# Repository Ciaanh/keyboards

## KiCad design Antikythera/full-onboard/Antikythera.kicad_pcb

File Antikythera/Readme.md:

http://www.keyboard-layout-editor.com/#/gists/16c88de775d4e0aa35cefe443daa3789

http://www.keyboard-layout-editor.com/
http://builder.swillkb.com/
https://github.com/badgeek/svg2shenzhen
inkscape
import svg in Kicad to place switches

Pin out
Atmega32u4

oled 2 pins
led 1 pin

Pro Micro

.   |  |  |  |  |  |    .
----|--|--|--|--|--|-----  
D3  |  |  |  |  |  |  RAW
D2  |  |  |  |  |  |  GND
GND |  |  |  |  |  |  RST
GND |  |  |  |  |  |  VCC
D1  |  |  |  |  |  |  F4
D0  |  |  |  |  |  |  F5
D4  |  |  |  |  |  |  F6
C6  |  |  |  |  |  |  F7
D7  |  |  |  |  |  |  B1
E6  |  |  |  |  |  |  B3
B4  |  |  |  |  |  |  B2
B5  |  |  |  |  |  |  B6

I/O => 18
15

Elite-C

.   |    |    |    |    |    |    .
----|----|----|----|----|----|-----  
D3  |    |    |    |    |    |  B0
D2  |    |    |    |    |    |  GND
GND |    |    |    |    |    |  RST
GND |    |    |    |    |    |  VCC
D1  |    |    |    |    |    |  F4
D0  |    |    |    |    |    |  F5
D4  |    |    |    |    |    |  F6
C6  |    |    |    |    |    |  F7
D7  |    |    |    |    |    |  B1
E6  |    |    |    |    |    |  B3
B4  |    |    |    |    |    |  B2
B5  | B7 | D5 | C7 | F1 | F0 |  B6

I/O => 24
21

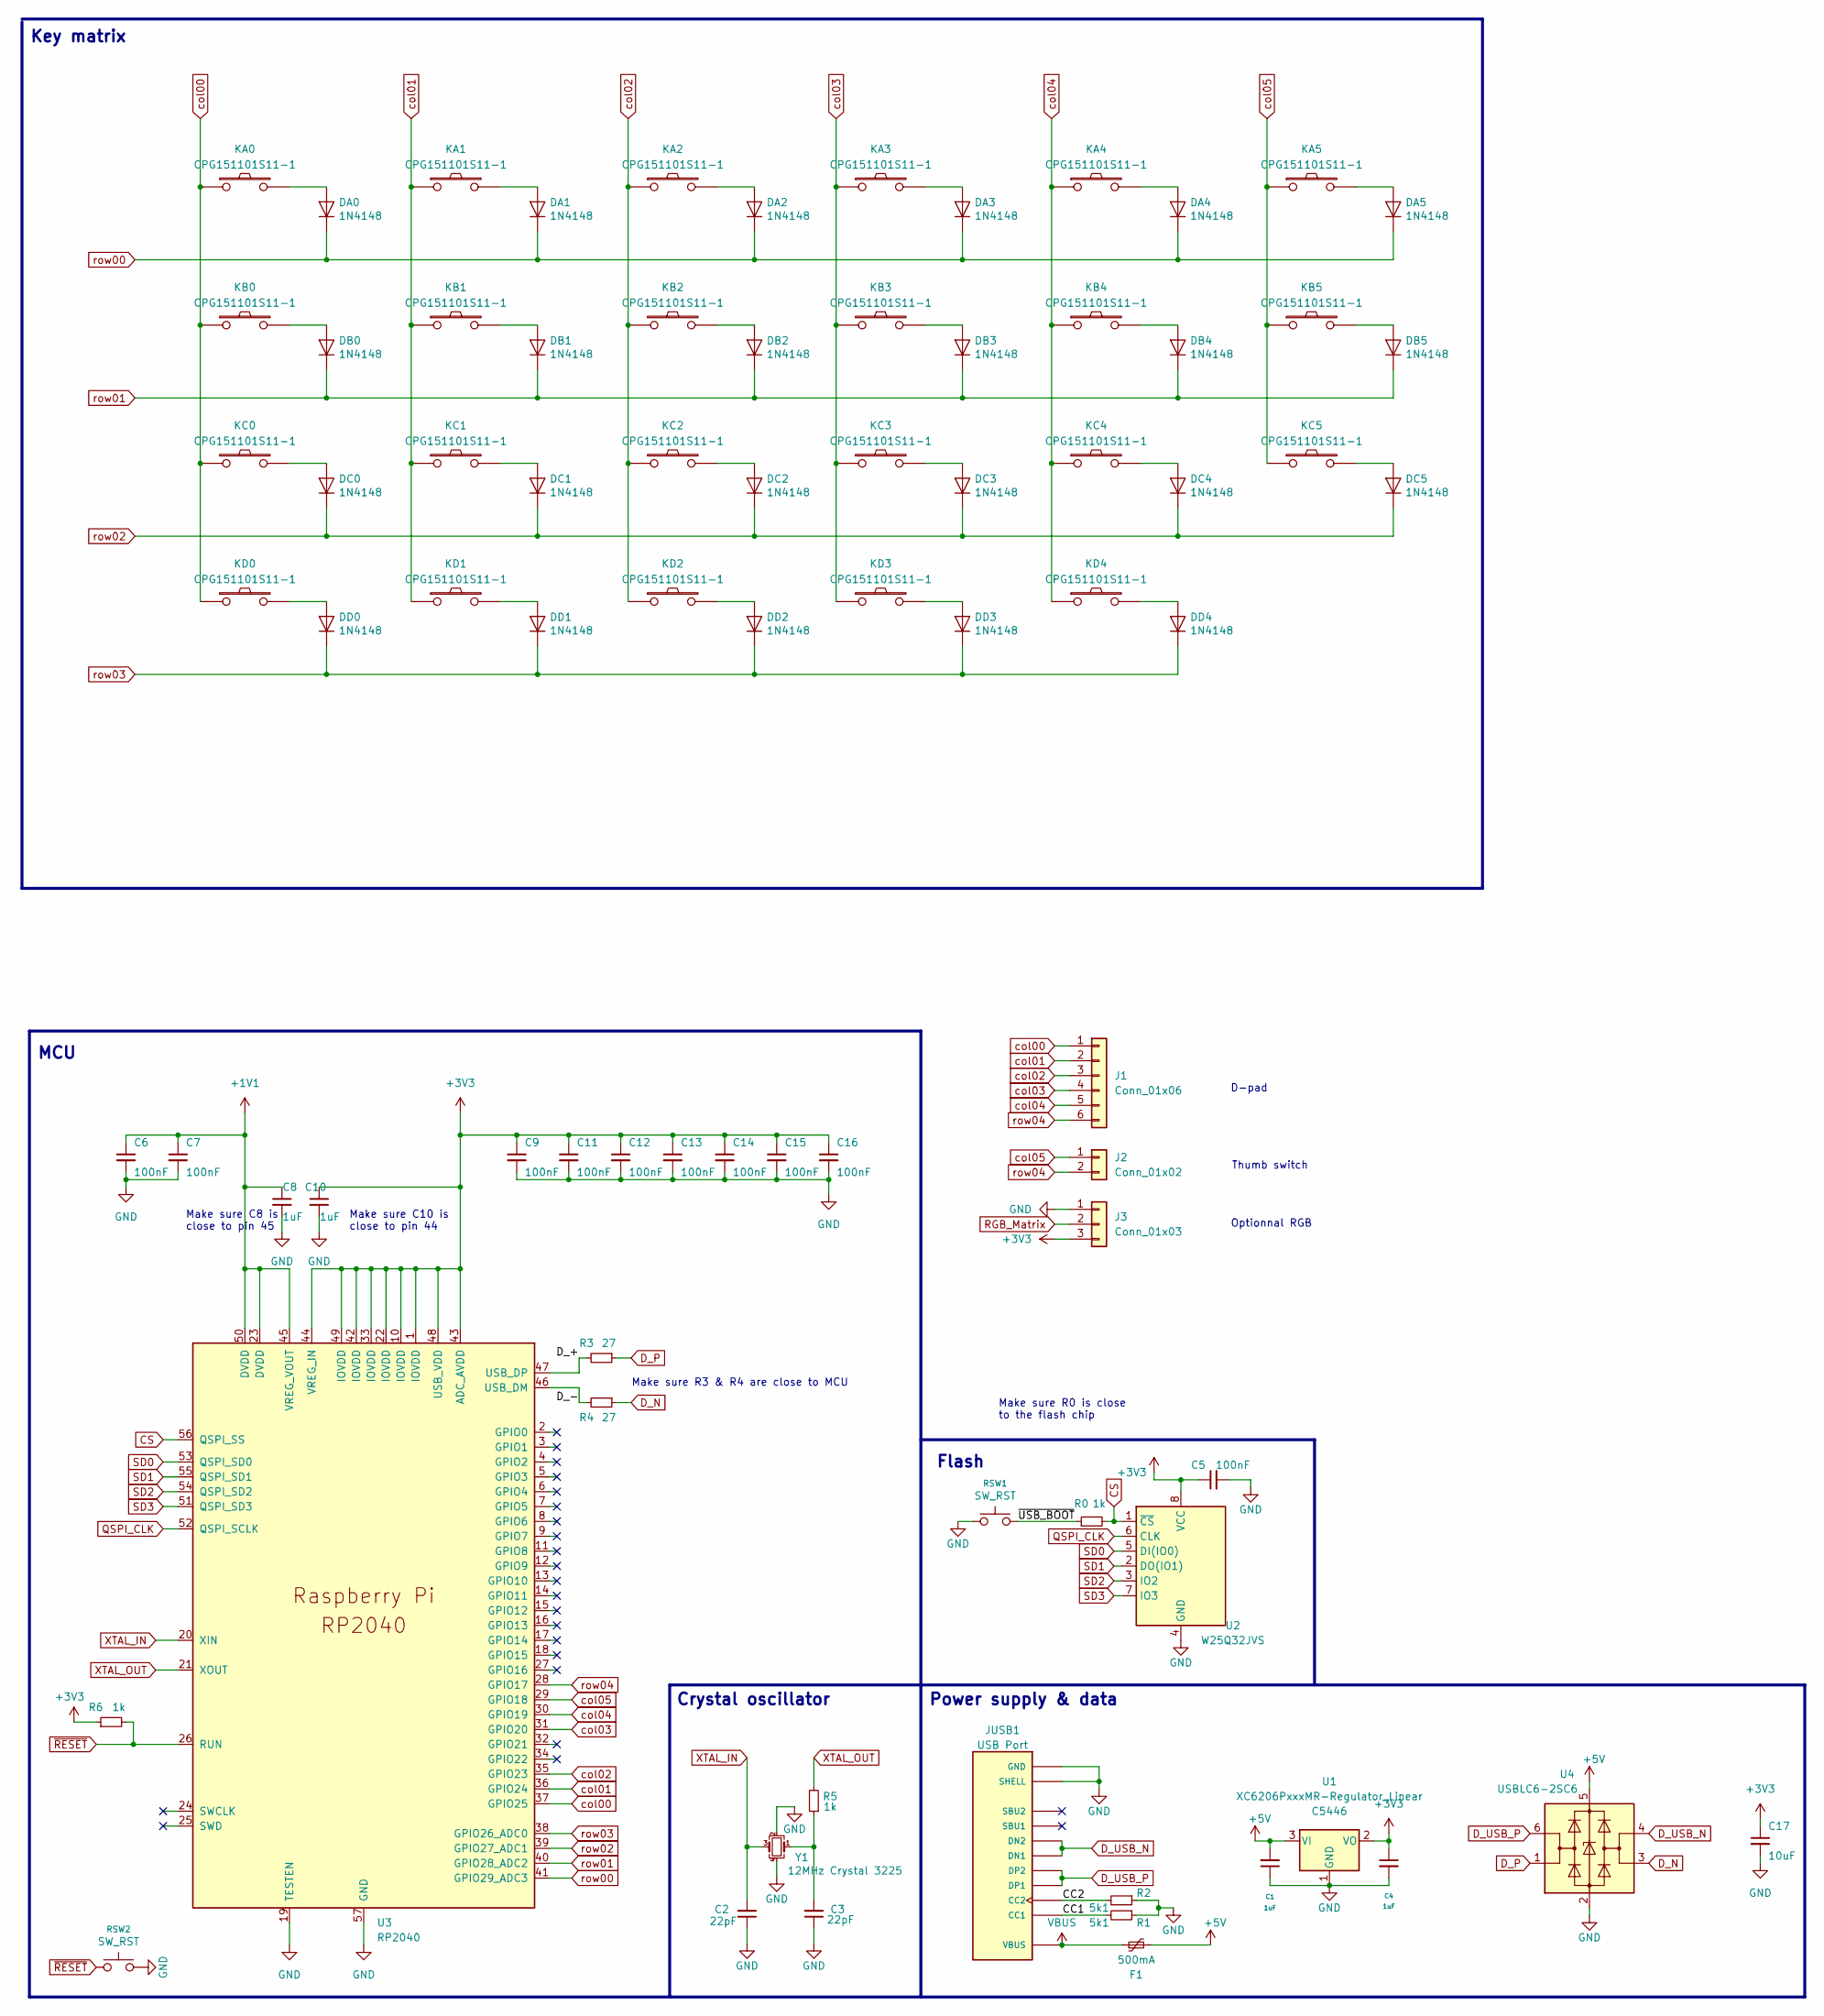
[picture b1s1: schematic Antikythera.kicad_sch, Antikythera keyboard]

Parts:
C1, C4, C8, C10: 1uF; C_0402_1005Metric; LCSC C52923
C2, C3: 22pF; C_0402_1005Metric; LCSC C1555
C5, C6, C7, C9, C11, C12, C13, C14, C15, C16: 100nF; C_0402_1005Metric; LCSC C1525
C17: 10uF; C_0402_1005Metric; LCSC C15525
DA0, DA1, DA2, DA3, DA4, DA5: 1N4148; D_SOD-123
DB0, DB1, DB2, DB3, DB4, DB5: 1N4148; D_SOD-123
DC0, DC1, DC2, DC3, DC4, DC5: 1N4148; D_SOD-123
DD0, DD1, DD2, DD3, DD4: 1N4148; D_SOD-123
F1: 500mA; Fuse_1206_3216Metric; LCSC C70076
J1: Conn_01x06; PinHeader_1x06_P2.54mm_Horizontal
J2: Conn_01x02
J3: Conn_01x03
JUSB1: USB Port; GCT_USB4085-GF-A_REVA4; PARTREV A4
KA0, KA1, KA2, KA3, KA4, KA5: CPG151101S11-1; SW_Gateron_KS_1.00u_Hotswap
KB0, KB1, KB2, KB3, KB4, KB5: CPG151101S11-1; SW_Gateron_KS_1.00u_Hotswap
KC0, KC1, KC2, KC3, KC4, KC5: CPG151101S11-1; SW_Gateron_KS_1.00u_Hotswap
KD0, KD1, KD2, KD3, KD4: CPG151101S11-1; SW_Gateron_KS_1.00u_Hotswap
R0, R5, R6: 1k; R_0402_1005Metric; LCSC C11702
R1, R2: 5k1; R_0402_1005Metric; LCSC C25905
R3, R4: 27; R_0402_1005Metric; LCSC C25190
RSW1, RSW2: SW_RST
U1: XC6206PxxxMR-Regulator_Linear; SOT-23; LCSC C5446
U2: W25Q32JVS; SOIC-8_5.23x5.23mm_P1.27mm
U3: RP2040; RP2040-QFN-56
U4: USBLC6-2SC6; SOT-23-6; LCSC C2827654
Y1: 12MHz Crystal 3225; Crystal_SMD_3225-4Pin_3.2x2.5mm; LCSC C9002

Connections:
+1V1: C6.1, C7.1, C8.1, U3.23 (DVDD), U3.45 (VREG_VOUT), U3.50 (DVDD)
+3V3: C4.1, C5.1, C9.1, C10.1, C11.1, C12.1, C13.1, C14.1, C15.1, C16.1, C17.1, J3.3, R6.1, U1.2 (VO), U2.8 (VCC), U3.1 (IOVDD), U3.10 (IOVDD), U3.22 (IOVDD), U3.33 (IOVDD), U3.42 (IOVDD), U3.43 (ADC_AVDD), U3.44 (VREG_IN), U3.48 (USB_VDD), U3.49 (IOVDD)
+5V: C1.2, F1.2, U1.3 (VI), U4.5 (VBUS)
/CC1: JUSB1.A5 (CC1), R1.2
/CC2: JUSB1.B5 (CC2), R2.2
/D_+: R3.2, U3.47 (USB_DP)
/D_-: R4.2, U3.46 (USB_DM)
/~USB_BOOT: R0.1, RSW1.2
CS: R0.2, U2.1 (~CS), U3.56 (QSPI_SS)
D_N: R4.1, U4.3 (I/O2)
D_P: R3.1, U4.1 (I/O1)
D_USB_N: JUSB1.A7 (DN1), JUSB1.B7 (DN2), U4.4 (I/O2)
D_USB_P: JUSB1.A6 (DP1), JUSB1.B6 (DP2), U4.6 (I/O1)
GND: C1.1, C2.1, C3.1, C4.2, C5.2, C6.2, C7.2, C8.2, C9.2, C10.2, C11.2, C12.2, C13.2, C14.2, C15.2, C16.2, C17.2, J3.1, JUSB1.A1 (GND), JUSB1.A12 (GND), JUSB1.B1 (GND), JUSB1.B12 (GND), JUSB1.P1 (SHELL), JUSB1.P2 (SHELL), JUSB1.P3 (SHELL), JUSB1.P4 (SHELL), R1.1, R2.1, RSW1.1, RSW2.2, U1.1 (GND), U2.4 (GND), U3.19 (TESTEN), U3.57 (GND), U4.2 (GND), Y1.2, Y1.4
unnamed: C3.2, R5.1, Y1.1
unnamed: DA0.2 (A), KA0.2
unnamed: DA1.2 (A), KA1.2
unnamed: DA2.2 (A), KA2.2
unnamed: DA3.2 (A), KA3.2
unnamed: DA4.2 (A), KA4.2
unnamed: DA5.2 (A), KA5.2
unnamed: DB0.2 (A), KB0.2
unnamed: DB1.2 (A), KB1.2
unnamed: DB2.2 (A), KB2.2
unnamed: DB3.2 (A), KB3.2
unnamed: DB4.2 (A), KB4.2
unnamed: DB5.2 (A), KB5.2
unnamed: DC0.2 (A), KC0.2
unnamed: DC1.2 (A), KC1.2
unnamed: DC2.2 (A), KC2.2
unnamed: DC3.2 (A), KC3.2
unnamed: DC4.2 (A), KC4.2
unnamed: DC5.2 (A), KC5.2
unnamed: DD0.2 (A), KD0.2
unnamed: DD1.2 (A), KD1.2
unnamed: DD2.2 (A), KD2.2
unnamed: DD3.2 (A), KD3.2
unnamed: DD4.2 (A), KD4.2
QSPI_CLK: U2.6 (CLK), U3.52 (QSPI_SCLK)
SD0: U2.5 (DI(IO0)), U3.53 (QSPI_SD0)
SD1: U2.2 (DO(IO1)), U3.55 (QSPI_SD1)
SD2: U2.3 (IO2), U3.54 (QSPI_SD2)
SD3: U2.7 (IO3), U3.51 (QSPI_SD3)
VBUS: F1.1, JUSB1.A4 (VBUS), JUSB1.A9 (VBUS), JUSB1.B4 (VBUS), JUSB1.B9 (VBUS)
XTAL_IN: C2.2, U3.20 (XIN), Y1.3
XTAL_OUT: R5.2, U3.21 (XOUT)
col00: J1.1, KA0.1, KB0.1, KC0.1, KD0.1, U3.37 (GPIO25)
col01: J1.2, KA1.1, KB1.1, KC1.1, KD1.1, U3.36 (GPIO24)
col02: J1.3, KA2.1, KB2.1, KC2.1, KD2.1, U3.35 (GPIO23)
col03: J1.4, KA3.1, KB3.1, KC3.1, KD3.1, U3.31 (GPIO20)
col04: J1.5, KA4.1, KB4.1, KC4.1, KD4.1, U3.30 (GPIO19)
col05: J2.1, KA5.1, KB5.1, KC5.1, U3.29 (GPIO18)
row00: DA0.1 (K), DA1.1 (K), DA2.1 (K), DA3.1 (K), DA4.1 (K), DA5.1 (K), U3.41 (GPIO29_ADC3)
row01: DB0.1 (K), DB1.1 (K), DB2.1 (K), DB3.1 (K), DB4.1 (K), DB5.1 (K), U3.40 (GPIO28_ADC2)
row02: DC0.1 (K), DC1.1 (K), DC2.1 (K), DC3.1 (K), DC4.1 (K), DC5.1 (K), U3.39 (GPIO27_ADC1)
row03: DD0.1 (K), DD1.1 (K), DD2.1 (K), DD3.1 (K), DD4.1 (K), U3.38 (GPIO26_ADC0)
row04: J1.6, J2.2, U3.28 (GPIO17)
~RESET: R6.2, RSW2.1, U3.26 (RUN)

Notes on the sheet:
Make sure R3 & R4 are close to MCU
Optionnal RGB
Flash
D-pad
Key matrix
MCU
Make sure C8 is close to pin 45
Make sure C10 is close to pin 44
Crystal oscillator
Make sure R0 is close to the flash chip
Thumb switch
Power supply & data

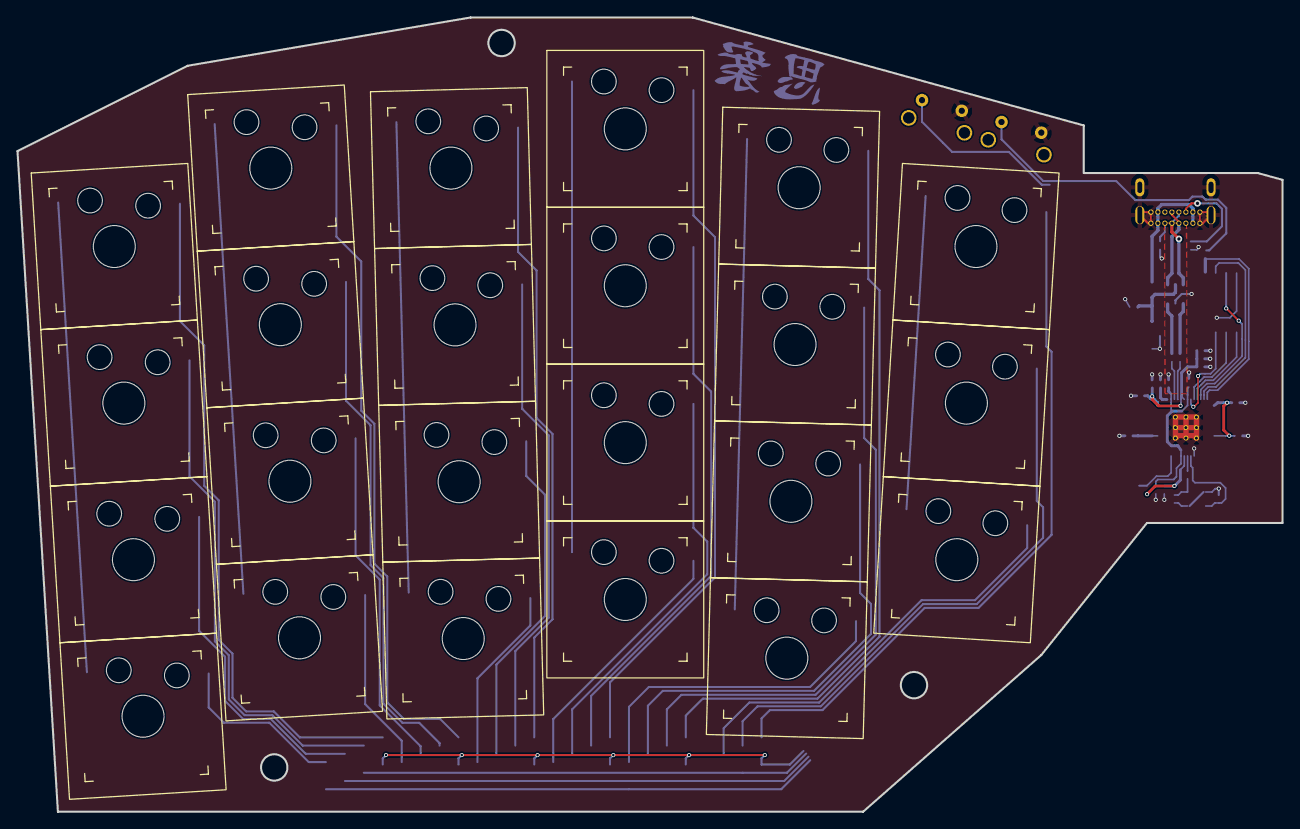
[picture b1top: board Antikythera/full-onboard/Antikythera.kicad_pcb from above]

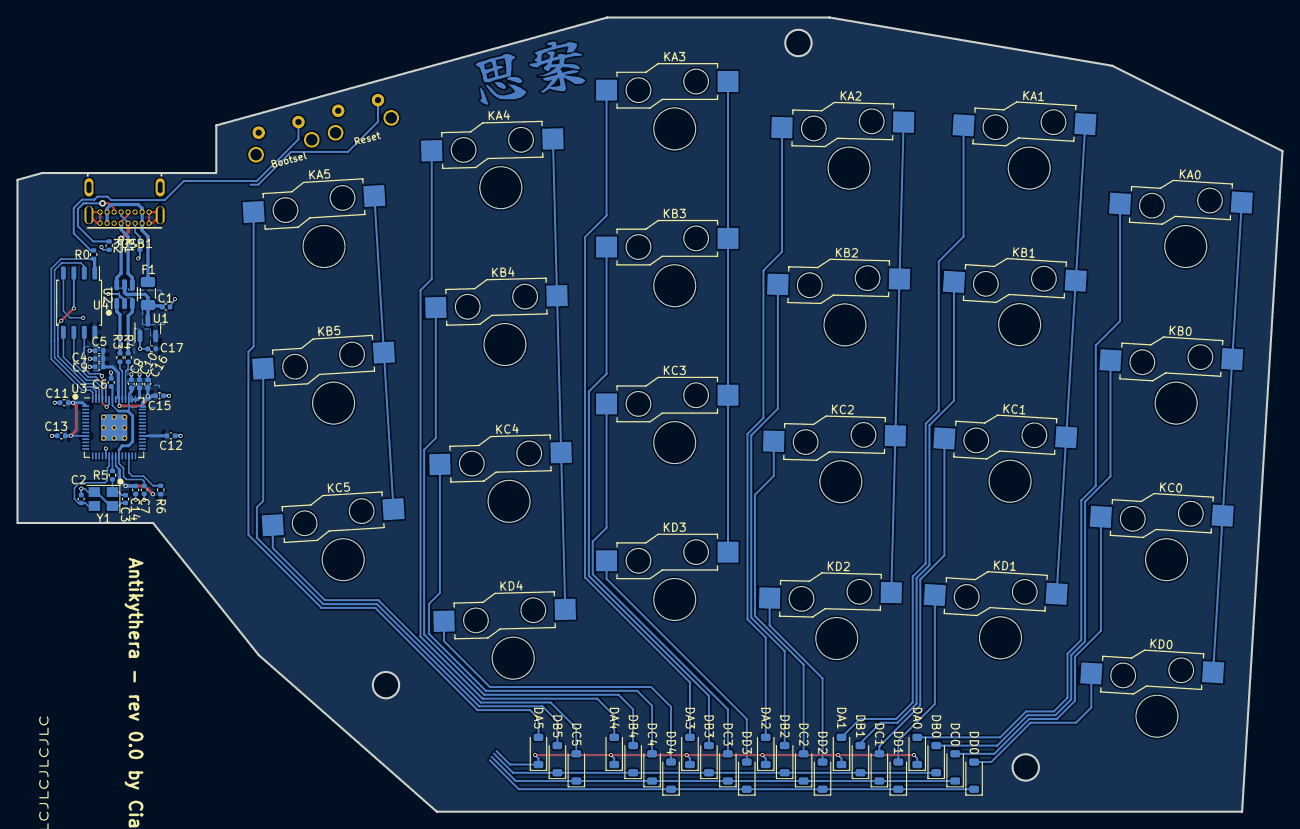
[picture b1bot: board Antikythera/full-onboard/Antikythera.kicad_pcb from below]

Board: 2 copper layers, 153.6 x 96.4 mm, 79 parts (55 on the bottom side), 57 nets.

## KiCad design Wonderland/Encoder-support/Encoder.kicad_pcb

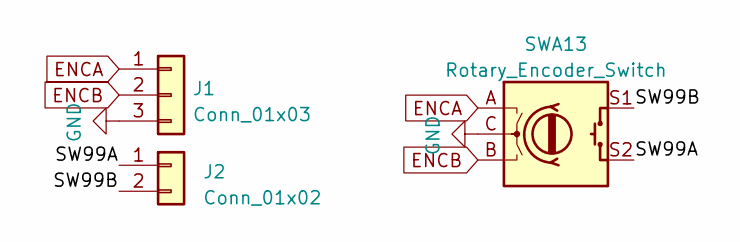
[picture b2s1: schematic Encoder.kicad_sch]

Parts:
J1: Conn_01x03; PinHeader_1x03_P2.54mm_Vertical
J2: Conn_01x02; PinHeader_1x02_P2.54mm_Vertical
SWA13: Rotary_Encoder_Switch; RotaryEncoder_EC11-Switch_Horizontal_H15mm

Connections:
/SW99A: J2.1, SWA13.S2
/SW99B: J2.2, SWA13.S1
ENCA: J1.1, SWA13.A
ENCB: J1.2, SWA13.B
GND: J1.3, SWA13.C

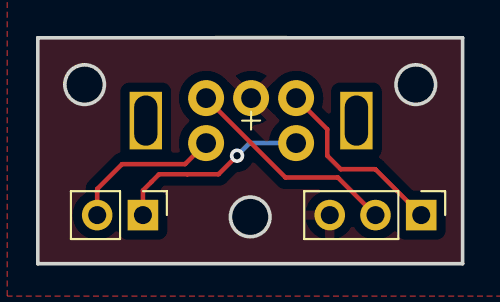
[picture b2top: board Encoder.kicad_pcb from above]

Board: 2 copper layers, 23.6 x 12.6 mm, 3 parts (0 on the bottom side), 5 nets.

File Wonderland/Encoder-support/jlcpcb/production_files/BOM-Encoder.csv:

Comment,Designator,Footprint,LCSC
Rotary_Encoder_Switch,SWA13,RotaryEncoder_EC11-Switch_Horizontal_H15mm,
Conn_01x02,J2,PinHeader_1x02_P2.54mm_Vertical,
Conn_01x03,J1,PinHeader_1x03_P2.54mm_Vertical,

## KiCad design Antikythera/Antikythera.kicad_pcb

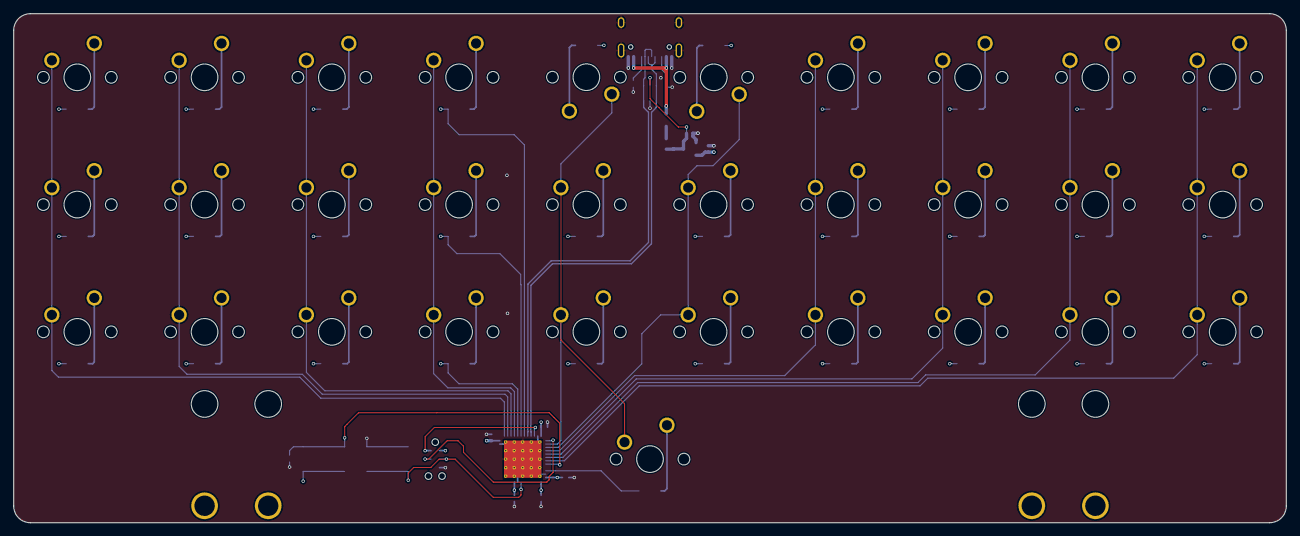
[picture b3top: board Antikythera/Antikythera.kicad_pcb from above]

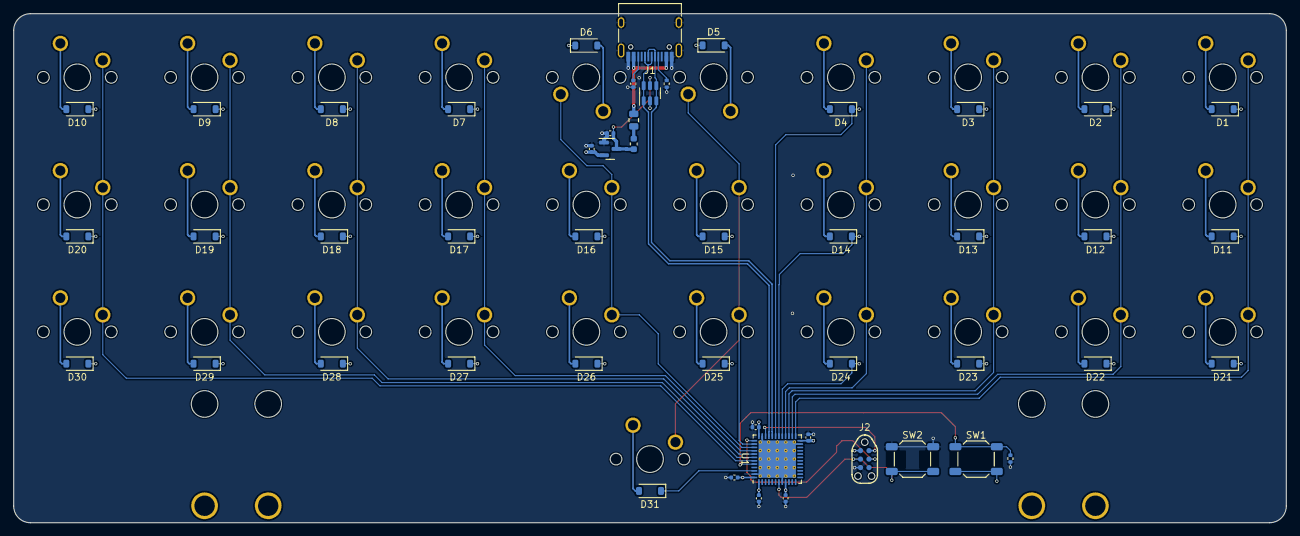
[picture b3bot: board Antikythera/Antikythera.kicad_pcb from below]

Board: 4 copper layers, 190.5 x 76.2 mm, 82 parts (50 on the bottom side), 58 nets.

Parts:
C1, C2: 1u; C_0402_1005Metric
C3: 4.7u; C_0402_1005Metric
C4, C5, C6, C7: 100n; C_0402_1005Metric
D1, D2, D3, D4, D5, D6, D7, D8, D9, D10, D11, D12, D13, D14, D15, D16, D17, D18, D19, D20, D21, D22, D23, D24, D25, D26, D27, D28, D29, D30, D31: D_Small; D_SOD-123
F1: 500mA; Fuse_0805_2012Metric
FB1: 100R @ 100 MHz; L_0603_1608Metric
J1: USB_C_Receptacle_USB2.0; USB_C_Receptacle_HRO_TYPE-C-31-M-12
J2: TC2030_SWD; CON_TC2030_outlined
MX1, MX2, MX3, MX4, MX5, MX6, MX7, MX8, MX9, MX10, MX11, MX12, MX13, MX14, MX15, MX16, MX17, MX18, MX19, MX20, MX21, MX22, MX23, MX24, MX25, MX26, MX27, MX28, MX29, MX30, MX31: Key_None; SW_MX_1u
R1, R2: 5.1k; R_0402_1005Metric
R3: 10k; R_0402_1005Metric
STAB31: Stab_None; STAB_MX_P_10u
SW1, SW2: SW_Push; SW_SPST_SKQG_WithStem
U1: STM32L443CCUx; QFN-48-1EP_7x7mm_P0.5mm_EP5.6x5.6mm_ThermalVias
U2: USBLC6-2SC6; SOT-23-6
U3: AP2127N-3.3; SOT-23

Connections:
+3.3V: C1.1, C3.1, C4.1, C5.1, C6.1, C7.1, J2.1 (VCC), SW1.2, U1.1 (VBAT), U1.9 (VDDA), U1.24 (VDD), U1.36 (VDDUSB), U1.48 (VDD), U3.2 (VO)
/BOOT0: R3.1, SW1.1, U1.44 (PH3)
/D+: J1.A6 (D+), J1.B6 (D+), U1.33 (PA12), U2.1 (I/O1), U2.6 (I/O1)
/D-: J1.A7 (D-), J1.B7 (D-), U1.32 (PA11), U2.3 (I/O2), U2.4 (I/O2)
/SWCLK: J2.4 (SWCLK), U1.37 (PA14)
/SWD: J2.2 (SWDIO), U1.34 (PA13)
/~RST: J2.3 (~RST), SW2.2, U1.7 (NRST)
COLUMN0: MX1.1, MX11.1, MX21.1, U1.25 (PB12)
COLUMN1: MX2.1, MX12.1, MX22.1, U1.26 (PB13)
COLUMN2: MX3.1, MX13.1, MX23.1, U1.27 (PB14)
COLUMN3: MX4.1, MX14.1, MX24.1, U1.28 (PB15)
COLUMN4: MX5.1, MX15.1, MX25.1, MX31.1, U1.38 (PA15)
COLUMN5: MX6.1, MX16.1, MX26.1, U1.39 (PB3)
COLUMN6: MX7.1, MX17.1, MX27.1, U1.40 (PB4)
COLUMN7: MX8.1, MX18.1, MX28.1, U1.41 (PB5)
COLUMN8: MX9.1, MX19.1, MX29.1, U1.42 (PB6)
COLUMN9: MX10.1, MX20.1, MX30.1, U1.43 (PB7)
GND: C1.2, C2.2, C3.2, C4.2, C5.2, C6.2, C7.2, J1.A1 (GND), J1.A12 (GND), J1.B1 (GND), J1.B12 (GND), J1.S1 (SHIELD), J2.5 (GND), R1.2, R2.2, R3.2, SW2.1, U1.8 (VSSA), U1.23 (VSS), U1.35 (VSS), U1.47 (VSS), U1.49 (VSS), U2.2 (GND), U3.1 (GND)
unnamed: D1.2 (A), MX1.2
unnamed: D2.2 (A), MX2.2
unnamed: D3.2 (A), MX3.2
unnamed: D4.2 (A), MX4.2
unnamed: D5.2 (A), MX5.2
unnamed: D6.2 (A), MX6.2
unnamed: D7.2 (A), MX7.2
unnamed: D8.2 (A), MX8.2
unnamed: D9.2 (A), MX9.2
unnamed: D10.2 (A), MX10.2
unnamed: D11.2 (A), MX11.2
unnamed: D12.2 (A), MX12.2
unnamed: D13.2 (A), MX13.2
unnamed: D14.2 (A), MX14.2
unnamed: D15.2 (A), MX15.2
unnamed: D16.2 (A), MX16.2
unnamed: D17.2 (A), MX17.2
unnamed: D18.2 (A), MX18.2
unnamed: D19.2 (A), MX19.2
unnamed: D20.2 (A), MX20.2
unnamed: D21.2 (A), MX21.2
unnamed: D22.2 (A), MX22.2
unnamed: D23.2 (A), MX23.2
unnamed: D24.2 (A), MX24.2
unnamed: D25.2 (A), MX25.2
unnamed: D26.2 (A), MX26.2
unnamed: D27.2 (A), MX27.2
unnamed: D28.2 (A), MX28.2
unnamed: D29.2 (A), MX29.2
unnamed: D30.2 (A), MX30.2
unnamed: D31.2 (A), MX31.2
unnamed: F1.1, J1.A4 (VBUS), J1.A9 (VBUS), J1.B4 (VBUS), J1.B9 (VBUS)
unnamed: F1.2, FB1.1
unnamed: J1.A5 (CC1), R1.1
unnamed: J1.B5 (CC2), R2.1
ROW0: D1.1 (K), D2.1 (K), D3.1 (K), D4.1 (K), D5.1 (K), D6.1 (K), D7.1 (K), D8.1 (K), D9.1 (K), D10.1 (K), U1.31 (PA10)
ROW1: D11.1 (K), D12.1 (K), D13.1 (K), D14.1 (K), D15.1 (K), D16.1 (K), D17.1 (K), D18.1 (K), D19.1 (K), D20.1 (K), U1.30 (PA9)
ROW2: D21.1 (K), D22.1 (K), D23.1 (K), D24.1 (K), D25.1 (K), D26.1 (K), D27.1 (K), D28.1 (K), D29.1 (K), D30.1 (K), U1.29 (PA8)
ROW3: D31.1 (K), U1.46 (PB9)
VBUS: C2.1, FB1.2, U2.5 (VBUS), U3.3 (VI)

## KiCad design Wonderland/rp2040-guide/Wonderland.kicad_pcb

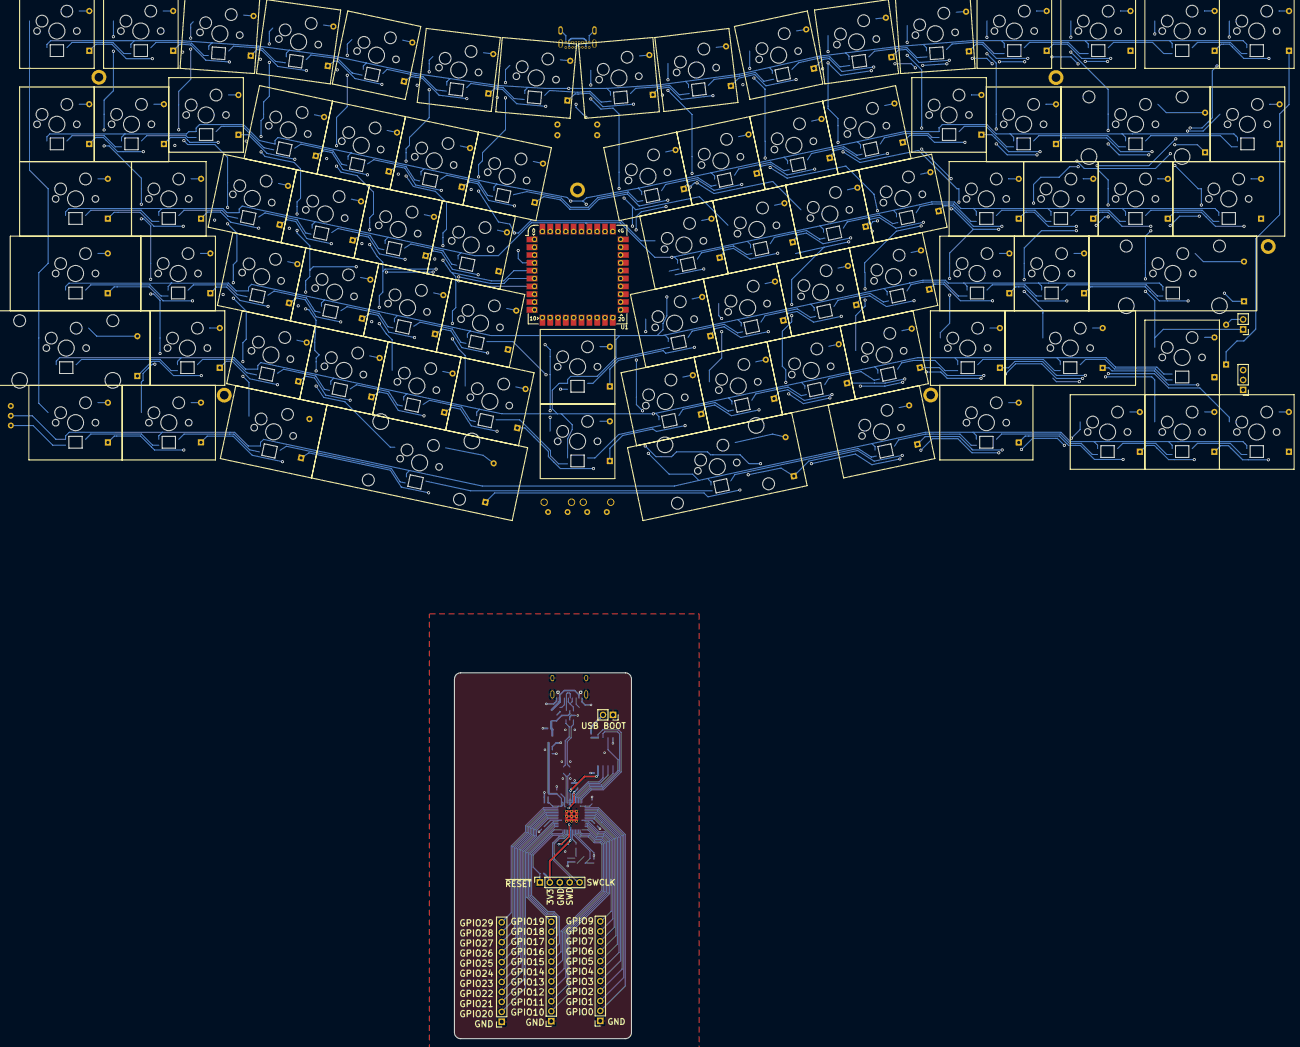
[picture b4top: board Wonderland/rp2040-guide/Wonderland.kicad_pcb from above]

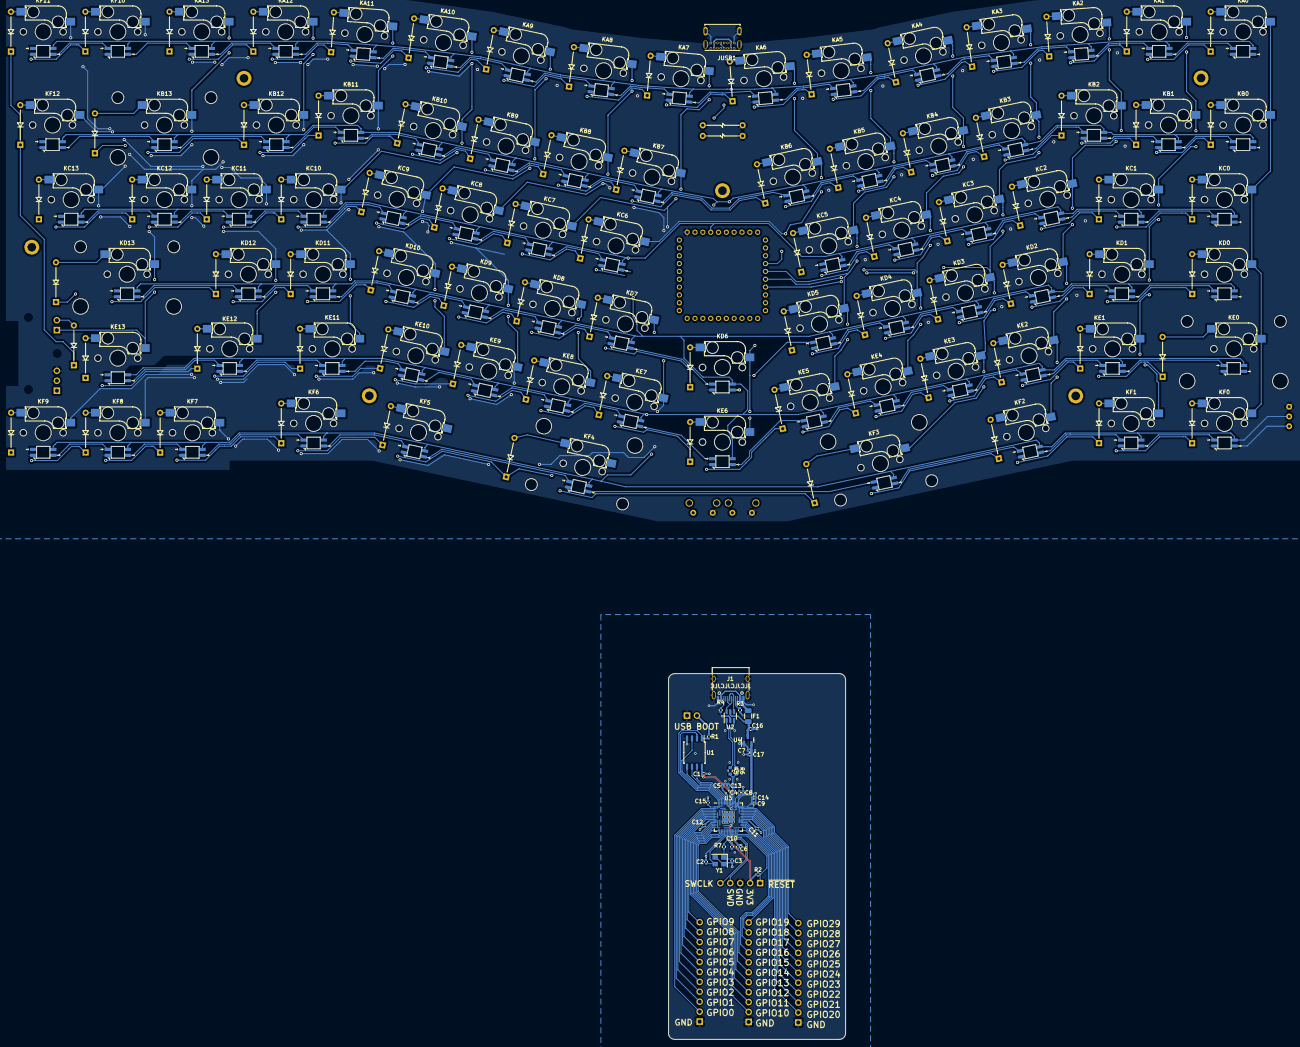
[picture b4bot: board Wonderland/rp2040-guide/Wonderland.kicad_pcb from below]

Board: 2 copper layers, 309.8 x 253.8 mm, 218 parts (32 on the bottom side), 56 nets.

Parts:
C1, C5, C6, C9, C10, C11, C12, C13, C14, C15: 100nF; C_0402_1005Metric
C2, C3: 22pF; C_0402_1005Metric
C4, C8, C16, C17: 1uF; C_0402_1005Metric
C7: 10uF; C_0402_1005Metric
DA0, DA1, DA2, DA3, DA4, DA5, DA6, DA7, DA8, DA9, DA10, DA11, DA12, DA13: D; Diode_THT
DB0, DB1, DB2, DB3, DB4, DB5, DB6, DB7, DB8, DB9, DB10, DB11, DB12, DB13: D; Diode_THT
DC0, DC1, DC2, DC3, DC4, DC5, DC6, DC7, DC8, DC9, DC10, DC11, DC12, DC13: D; Diode_THT
DD0, DD1, DD2, DD3, DD4, DD5, DD6, DD7, DD8, DD9, DD10, DD11, DD12, DD13: D; Diode_THT
DE0, DE1, DE2, DE3, DE4, DE5, DE6, DE7, DE8, DE9, DE10, DE11, DE12, DE13: D; Diode_THT
DF0, DF1, DF2, DF3, DF4, DF5, DF6, DF7, DF8, DF9, DF10, DF11, DF12, DF13: D; Diode_THT
F1: 500mA; Fuse_1206_3216Metric
J1: Conn_01x03; PinHeader_1x03_P2.54mm_Vertical
J1#2: USB_C_Receptacle_USB2.0; USB_C_Receptacle_HRO_TYPE-C-31-M-12
J2: SWD; PinSocket_1x05_P2.54mm_Vertical
J2#2: Conn_01x02; PinHeader_1x02_P2.54mm_Vertical
J3, J4#2, J5: Conn_01x11; PinSocket_1x11_P2.54mm_Vertical
J4: Conn_01x03; conn_3pins
JUSB1: USB Port; GCT_USB4085-GF-A_REVA4
KA0, KA1, KA2, KA3, KA4, KA5, KA6, KA7, KA8, KA9, KA10, KA11, KA12, KA13: KEY_SW; SW_Cherry_MX_1.00u_SK6812MINI-E_Hotswap
KB0, KB1, KB2, KB3, KB4, KB5, KB6, KB7, KB8, KB9, KB10, KB11, KB12: KEY_SW; SW_Cherry_MX_1.00u_SK6812MINI-E_Hotswap
KB13: KEY_SW; SW_Cherry_MX_2.00u_SK6812MINI-E_Hotswap
KC0, KC13: KEY_SW; SW_Cherry_MX_1.50u_SK6812MINI-E_Hotswap
KC1, KC2, KC3, KC4, KC5, KC6, KC7, KC8, KC9, KC10, KC11, KC12: KEY_SW; SW_Cherry_MX_1.00u_SK6812MINI-E_Hotswap
KD0: KEY_SW; SW_Cherry_MX_1.75u_SK6812MINI-E_Hotswap
KD1, KD2, KD3, KD4, KD5, KD6, KD7, KD8, KD9, KD10, KD11, KD12: KEY_SW; SW_Cherry_MX_1.00u_SK6812MINI-E_Hotswap
KD13: KEY_SW; SW_Cherry_MX_2.25u_SK6812MINI-E_Hotswap
KE0: KEY_SW; SW_Cherry_MX_2.25u_SK6812MINI-E_Hotswap
KE1, KE2, KE3, KE4, KE5, KE6, KE7, KE8, KE9, KE10, KE11, KE13: KEY_SW; SW_Cherry_MX_1.00u_SK6812MINI-E_Hotswap
KE12: KEY_SW; SW_Cherry_MX_1.75u_SK6812MINI-E_Hotswap
KF0, KF1, KF2, KF5, KF6: KEY_SW; SW_Cherry_MX_1.25u_SK6812MINI-E_Hotswap
KF3: KEY_SW; SW_Cherry_MX_2.75u_SK6812MINI-E_Hotswap_Reversed
KF4: KEY_SW; SW_Cherry_MX_2.25u_SK6812MINI-E_Hotswap_Reversed
KF7, KF8, KF9, KF10, KF11, KF12: KEY_SW; SW_Cherry_MX_1.00u_SK6812MINI-E_Hotswap
MountTopMiddle1, MountTopMiddle2, MountTopMiddle3, MountTopMiddle4, MountTopMiddle5, MountTopMiddle6: MountingHole; MountingHole_2.2mm_M2_Pad
R1, R2: 5.1k; Resistors_THT
R1#2, R2#2, R7: 1k; R_0402_1005Metric
R3, R4: 5k1; R_0402_1005Metric
R5, R6: 27R; R_0603_1608Metric
RSW0, RSW1: SW_RST
SW1: SW_Push; PinSocket_1x02_P2.54mm_Vertical
U1: RP2040_Stamp; RP2040_Stamp_THT
U1#2: W25Q128JVS; SOIC-8_5.23x5.23mm_P1.27mm
U2: USBLC6-2SC6; SOT-23-6
U3: RP2040; RP2040-QFN-56
U4: XC6206PxxxMR-Regulator_Linear; SOT-23
Y1: 12MHz; Crystal_SMD_3225-4Pin_3.2x2.5mm

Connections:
+1V1: C4.1, C5.1, C6.1, U3.23 (DVDD), U3.45 (VREG_VOUT), U3.50 (DVDD)
+3V3: C1.1, C7.1, C8.1, C9.1, C10.1, C11.1, C12.1, C13.1, C14.1, C15.1, C17.2, J2.2, R2#2.1, U1#2.8 (VCC), U3.1 (IOVDD), U3.10 (IOVDD), U3.22 (IOVDD), U3.33 (IOVDD), U3.42 (IOVDD), U3.43 (ADC_AVDD), U3.44 (VREG_VIN), U3.48 (USB_VDD), U3.49 (IOVDD), U4.2 (VO)
+5V: C16.2, F1.2, JUSB1.A4 (VBUS), JUSB1.A9 (VBUS), JUSB1.B4 (VBUS), JUSB1.B9 (VBUS), U1.33 (5V), U2.5 (VBUS), U4.3 (VI)
/CC1: J1#2.A5 (CC1), R3.1
/CC2: J1#2.B5 (CC2), R4.1
/D_+: R5.2, U3.47 (D+)
/D_-: R6.2, U3.46 (D-)
/GPIO0: J5.2, U3.2 (GPIO0)
/GPIO1: J5.3, U3.3 (GPIO1)
/GPIO2: J5.4, U3.4 (GPIO2)
/GPIO3: J5.5, U3.5 (GPIO3)
/GPIO4: J5.6, U3.6 (GPIO4)
/GPIO5: J5.7, U3.7 (GPIO5)
/GPIO6: J5.8, U3.8 (GPIO6)
/GPIO7: J5.9, U3.9 (GPIO7)
/GPIO8: J5.10, U3.11 (GPIO8)
/GPIO9: J5.11, U3.12 (GPIO9)
/GPIO10: J4#2.2, U3.13 (GPIO10)
/GPIO11: J4#2.3, U3.14 (GPIO11)
/GPIO12: J4#2.4, U3.15 (GPIO12)
/GPIO13: J4#2.5, U3.16 (GPIO13)
/GPIO14: J4#2.6, U3.17 (GPIO14)
/GPIO15: J4#2.7, U3.18 (GPIO15)
/GPIO16: J4#2.8, U3.27 (GPIO16)
/GPIO17: J4#2.9, U3.28 (GPIO17)
/GPIO18: J4#2.10, U3.29 (GPIO18)
/GPIO19: J4#2.11, U3.30 (GPIO19)
/GPIO20: J3.2, U3.31 (GPIO20)
/GPIO21: J3.3, U3.32 (GPIO21)
/GPIO22: J3.4, U3.34 (GPIO22)
/GPIO23: J3.5, U3.35 (GPIO23)
/GPIO24: J3.6, U3.36 (GPIO24)
/GPIO25: J3.7, U3.37 (GPIO25)
/GPIO26: J3.8, U3.38 (GPIO26/ADC0)
/GPIO27: J3.9, U3.39 (GPIO27/ADC1)
/GPIO28: J3.10, U3.40 (GPIO28/ADC2)
/GPIO29: J3.11, U3.41 (GPIO29/ADC3)
/XTAL_O: C3.2, R7.1, Y1.1
/~USB_BOOT: R1#2.1, SW1.2
CS: R1#2.2, U1#2.1 (~CS), U3.56 (QSPI_SS_N)
D_N: R6.1, U2.3 (I/O2)
D_P: R5.1, U2.1 (I/O1)
D_USB_N: J1#2.A7 (D-), J1#2.B7 (D-), U2.4 (I/O2)
D_USB_P: J1#2.A6 (D+), J1#2.B6 (D+), U2.6 (I/O1)
GND: C1.2, C2.1, C3.1, C4.2, C5.2, C6.2, C7.2, C8.2, C9.2, C10.2, C11.2, C12.2, C13.2, C14.2, C15.2, C16.1, C17.1, J1.3, J1#2.A1 (GND), J1#2.A12 (GND), J1#2.B1 (GND), J1#2.B12 (GND), J1#2.S1 (SHIELD), J2.3, J3.1, J4.3, J4#2.1, J5.1, JUSB1.A1 (GND), JUSB1.A12 (GND), JUSB1.B1 (GND), JUSB1.B12 (GND), JUSB1.P1 (SHELL), JUSB1.P2 (SHELL), JUSB1.P3 (SHELL), JUSB1.P4 (SHELL), KA0.5 (GND), KA1.5 (GND), KA2.5 (GND), KA3.5 (GND), KA4.5 (GND), KA5.5 (GND), KA6.5 (GND), KA7.5 (GND), KA8.5 (GND), KA9.5 (GND), KA10.5 (GND), KA11.5 (GND), KA12.5 (GND), KA13.5 (GND), KB0.5 (GND), KB1.5 (GND), KB2.5 (GND), KB3.5 (GND), KB4.5 (GND), KB5.5 (GND), KB6.5 (GND), KB7.5 (GND), KB8.5 (GND), KB9.5 (GND), KB10.5 (GND), KB11.5 (GND), KB12.5 (GND), KB13.5 (GND), KC0.5 (GND), KC1.5 (GND), KC2.5 (GND), KC3.5 (GND), KC4.5 (GND), KC5.5 (GND), KC6.5 (GND), KC7.5 (GND), KC8.5 (GND), KC9.5 (GND), KC10.5 (GND), KC11.5 (GND), KC12.5 (GND), KC13.5 (GND), KD0.5 (GND), KD1.5 (GND), KD2.5 (GND), KD3.5 (GND), KD4.5 (GND), KD5.5 (GND), KD6.5 (GND), KD7.5 (GND), KD8.5 (GND), KD9.5 (GND), KD10.5 (GND), KD11.5 (GND), KD12.5 (GND), KD13.5 (GND), KE0.5 (GND), KE1.5 (GND), KE2.5 (GND), KE3.5 (GND), KE4.5 (GND), KE5.5 (GND), KE6.5 (GND), KE7.5 (GND), KE8.5 (GND), KE9.5 (GND), KE10.5 (GND), KE11.5 (GND), KE12.5 (GND), KE13.5 (GND), KF0.5 (GND), KF1.5 (GND), KF2.5 (GND), KF3.5 (GND), KF4.5 (GND), KF5.5 (GND), KF6.5 (GND), KF7.5 (GND), KF8.5 (GND), KF9.5 (GND), KF10.5 (GND), KF11.5 (GND), KF12.5 (GND), R1.1, R2.1, R3.2, R4.2, RSW0.2, RSW1.2, SW1.1, U1.31 (GND), U1#2.4 (GND), U2.2 (GND), U3.19 (TESTEN), U3.57 (GND), U4.1 (GND), Y1.2, Y1.4
QSPI_CLK: U1#2.6 (CLK), U3.52 (QSPI_SCLK)
SD0: U1#2.5 (DI(IO0)), U3.53 (QSPI_SD0)
SD1: U1#2.2 (DO(IO1)), U3.55 (QSPI_SD1)
SD2: U1#2.3 (IO2), U3.54 (QSPI_SD2)
SD3: U1#2.7 (IO3), U3.51 (QSPI_SD3)
SWCLK: J2.5, U3.24 (SWCLK)
SWD: J2.4, U3.25 (SWDIO)
VBUS: F1.1, J1#2.A4 (VBUS), J1#2.A9 (VBUS), J1#2.B4 (VBUS), J1#2.B9 (VBUS)
XTAL_IN: C2.2, U3.20 (XTAL_IN), Y1.3
XTAL_OUT: R7.2, U3.21 (XTAL_OUT)
~RESET: J2.1, R2#2.2, U3.26 (~RUN)

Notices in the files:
Wonderland/rpi-pico-debugger-shoe-master/hardware/rpi-pico-debugger-shoe/rpi-pico-debugger-shoe.kicad_pcb:
https://creativecommons.org/licenses/by/4.0
License: CC BY 4.0
parts and their libraries:
Copyright 2016 Accelerated Designs. All rights reserved.
